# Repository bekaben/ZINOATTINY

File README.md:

# ZINOATTINY : 

<p align="justify">
ZINOATTINY is a low-cost ATTINY85 Board that's compatible with ARDUINO IDE. 
<BR>Designed in KICAD by Belkacem BENADDA for IACUBEE.</p>

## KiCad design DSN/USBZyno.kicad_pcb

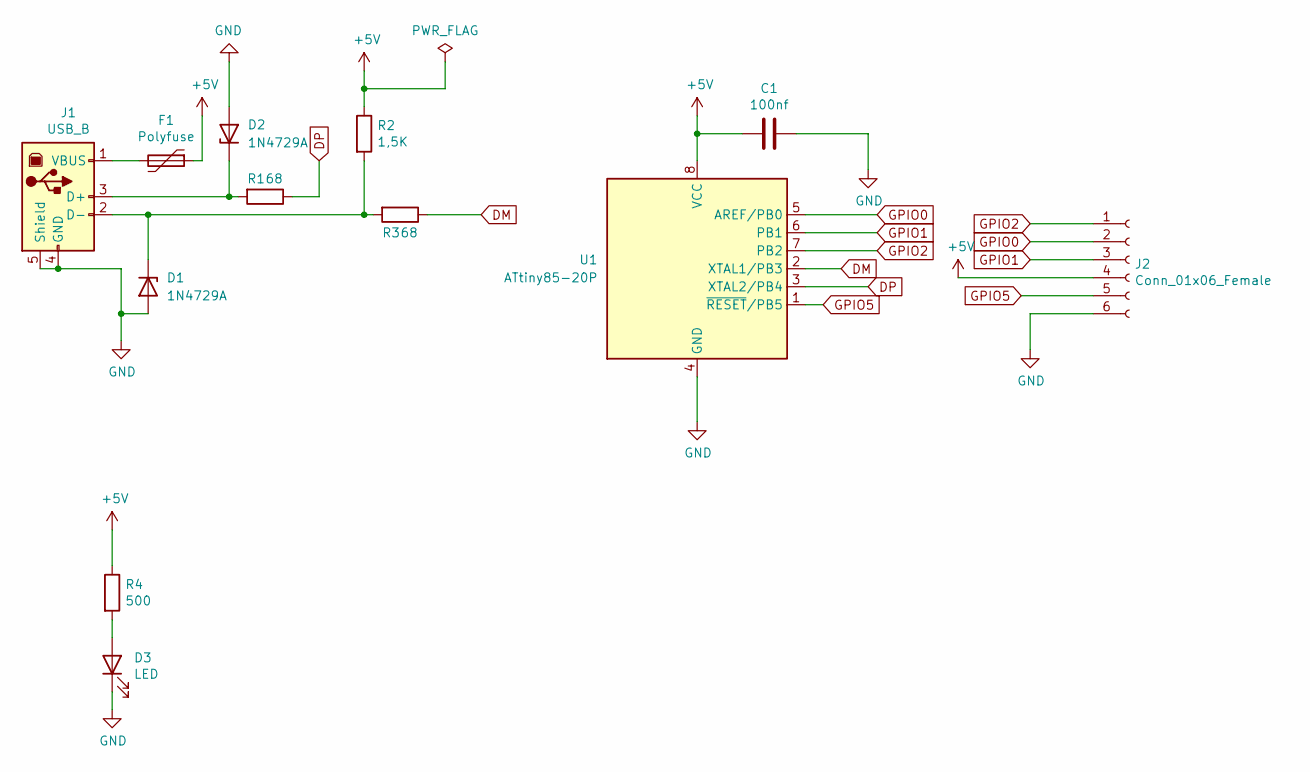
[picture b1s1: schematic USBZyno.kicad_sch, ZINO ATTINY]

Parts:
C1: 100nf; C_Disc_D5.0mm_W2.5mm_P5.00mm
D1, D2: 1N4729A; D_DO-35_SOD27_P7.62mm_Horizontal
D3: LED; LED_D3.0mm
F1: Polyfuse; C_Disc_D5.1mm_W3.2mm_P5.00mm
J1: USB_B; USB_B_OST_USB-B1HSxx_Horizontal
J2: Conn_01x06_Female; PinSocket_1x06_P2.54mm_Vertical
R1, R3: 68; R_Axial_DIN0204_L3.6mm_D1.6mm_P7.62mm_Horizontal
R2: 1,5K; R_Axial_DIN0204_L3.6mm_D1.6mm_P7.62mm_Horizontal
R4: 500; R_Axial_DIN0204_L3.6mm_D1.6mm_P7.62mm_Horizontal
U1: ATtiny85-20P; DIP-8_W7.62mm

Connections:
+5V: C1.2, F1.1, J2.4, R2.1, R4.1, U1.8 (VCC)
DM: R3.1, U1.2 (XTAL1/PB3)
DP: R1.1, U1.3 (XTAL2/PB4)
GND: C1.1, D1.2 (A), D2.2 (A), D3.1 (K), J1.4 (GND), J1.5 (Shield), J2.6, U1.4 (GND)
GPIO0: J2.2, U1.5 (AREF/PB0)
GPIO1: J2.3, U1.6 (PB1)
GPIO2: J2.1, U1.7 (PB2)
GPIO5: J2.5, U1.1 (~RESET/PB5)
unnamed: D1.1 (K), J1.2 (D-), R2.2, R3.2
unnamed: D2.1 (K), J1.3 (D+), R1.2
unnamed: D3.2 (A), R4.2
unnamed: F1.2, J1.1 (VBUS)

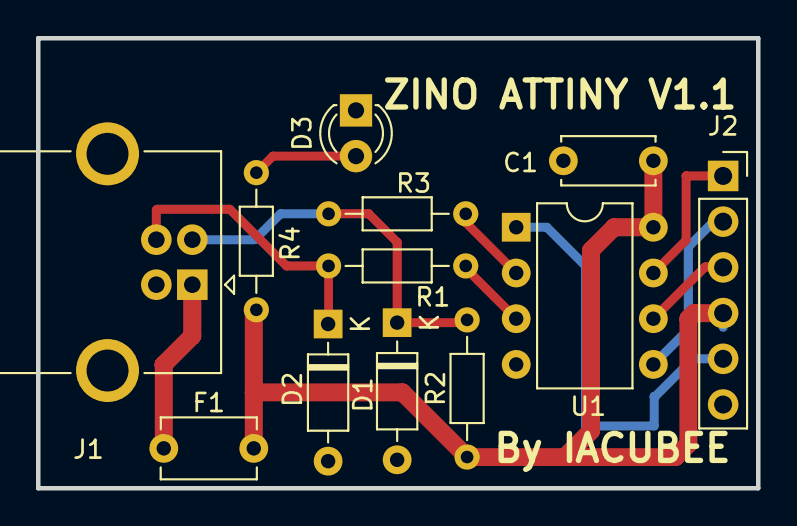
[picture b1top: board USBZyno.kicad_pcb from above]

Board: 2 copper layers, 40.0 x 25.0 mm, 12 parts (0 on the bottom side), 12 nets.

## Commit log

2022-08-31 Create Description
2022-08-31 Create tmp
